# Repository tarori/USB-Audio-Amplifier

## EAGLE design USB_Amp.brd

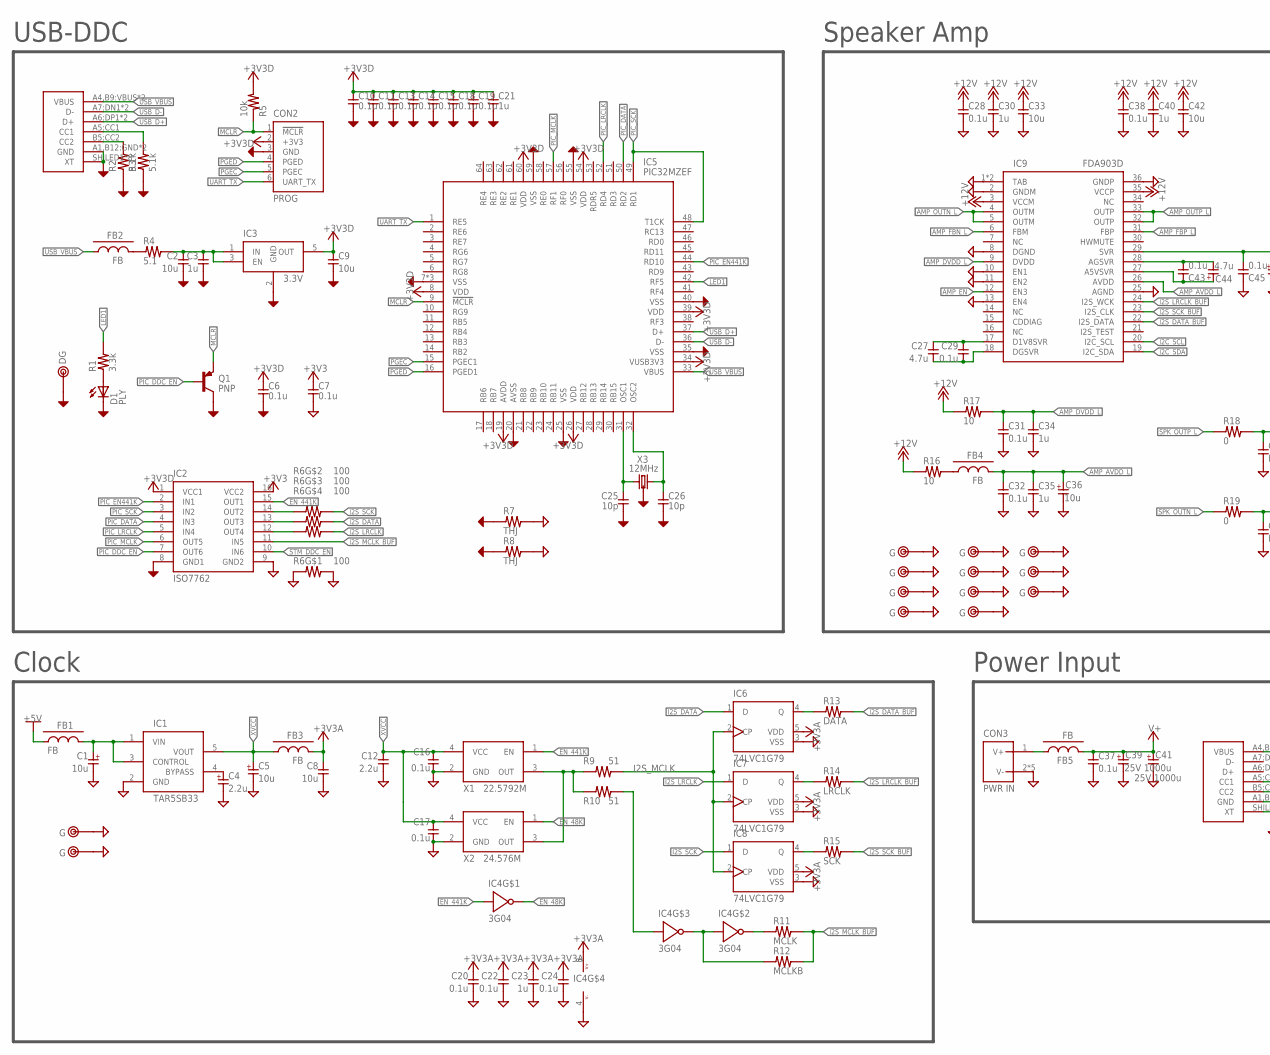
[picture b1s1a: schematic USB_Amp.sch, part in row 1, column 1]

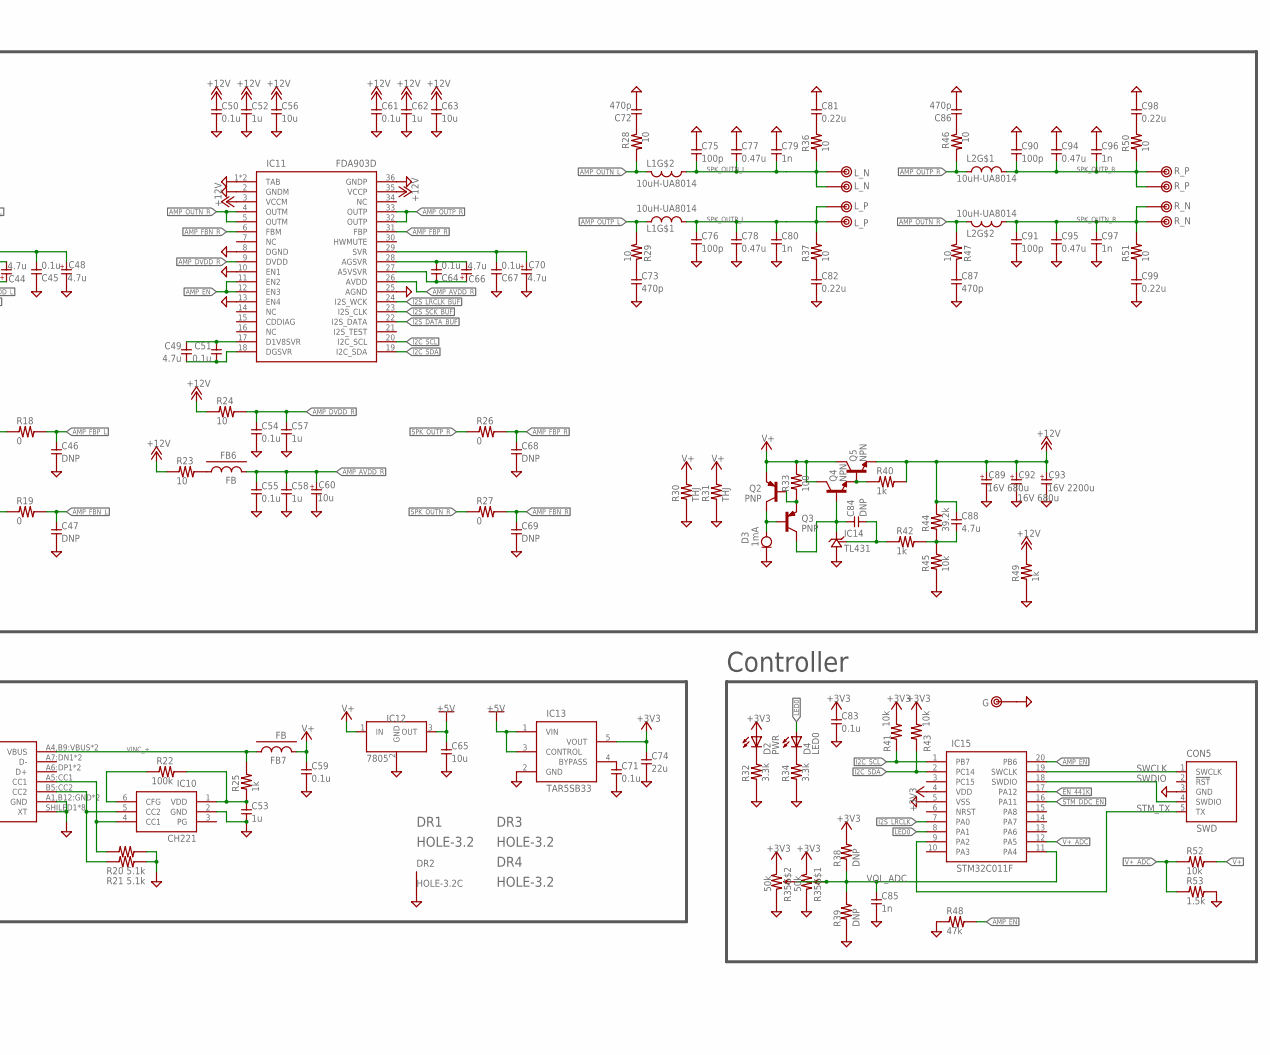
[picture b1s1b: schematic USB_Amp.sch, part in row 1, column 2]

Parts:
C1, C5: 10u; 2012-POL
C2, C8, C9: 10u; 2012
C3, C21, C53: 1u; 1608C
C4: 2.2u; 2012-POL
C6, C10, C11, C13, C14, C15, C16, C17, C18, C19, C37, C59, C71, C83: 0.1u; 1608C
C7, C20, C22, C24, C28, C29, C31, C32, C38, C43, C45, C50, C51, C54, C55, C61, C64, C67: 0.1u; 1005
C12: 2.2u; 2012
C23: 1u; 1005
C25, C26: 10p; 1005
C27, C49: 4.7u; 1608C
C30, C34, C35, C40, C52, C57, C58, C62: 1u; 2012
C33, C42, C56, C63: 10u; 3225
C36, C60: 10u; 3225-POL
C39, C41: 25V 1000u; E5-10
C44, C48, C66, C70: 4.7u; 2012-POL
C46, C47, C68, C69, C84: DNP; 1608C
C65: 10u; 3216
C72, C73, C86, C87: 470p; 1608C
C74: 22u; 2012
C75, C76, C90, C91: 100p; 1608C
C77, C78, C94, C95: 0.47u; C050W
C79, C80, C96, C97: 1n; 2012
C81, C82, C98, C99: 0.22u; 3225
C85: 1n; 1608C
C88: 4.7u; 3216
C89, C92: 16V 680u; E5-10
C93: 16V 2200u; E5-13
CON1: AUDIO_IN; 5077CR-16-SMC2-BK-TR-2OZ
CON2: PROG; 1X06
CON3: PWR IN; 2.1MM_CON
CON4: USB-C-2OZ; 5077CR-16-SMC2-BK-TR-2OZ
CON5: SWD; SWD_CON
D1: PLY; D1608
D2: PWR; LED2.5
D3: 1mA; SOD123
D4: LED0; LED2.5
DR1, DR3, DR4: HOLE-3.2; HOLE_3.2
DR2: HOLE-3.2C; HOLE_3.2_CON2
FB1, FB2, FB3, FB4, FB6: FB; 1608-FB
FB5, FB7: FB; 3216-FB
IC1, IC13: TAR5SB33; SOT23-5
IC2: ISO7762; TSSOP16
IC3: 3.3V; SOT23-5
IC4: 3G04; SSOP8-P-0.65
IC5: PIC32MZEF; QFN64HT
IC6, IC7, IC8: 74LVC1G79; TSSOP5
IC9, IC11: FDA903D; POWER-SSO36
IC10: CH221; SOT23-6
IC12: 7805; DPAK
IC14: TL431; SC59
IC15: STM32C011F; TSSOP20
L1, L2: 10uH-UA8014; UA8014
Q1, Q2, Q3: PNP; SC59
Q4: NPN; SC59
Q5: NPN; SOT223
R1, R32, R34: 3.3k; 1608
R2, R3, R20, R21: 5.1k; 1608
R4: 5.1; 1608
R5, R41, R43, R45, R52: 10k; 1608
R6: 100; EXB28V
R7, R8: THJ; 3216-2
R9, R10: 51; 1005
R11: MCLK; 1005
R12: MCLKB; 1005
R13: DATA; 1005
R14: LRCLK; 1005
R15: SCK; 1005
R16, R17, R23, R24, R28, R29, R46, R47: 10; 1608
R18, R19, R26, R27: 0; 1608
R22: 100k; 1608
R25: 1k; 2012
R30, R31: THJ; 1608-W
R33: 100; 1608
R35: 50k; RK0972
R36, R37, R50, R51: 10; 3216
R38, R39: DNP; 1608
R40, R42: 1k; 1608
R44: 39.2k; 1608
R48: 47k; 1608
R49: 1k; 3216
R53: 1.5k; 1608
TP1: L_N; TESTPIN-BIG
TP2: L_P; TESTPIN-BIG
TP3: R_P; TESTPIN-BIG
TP4: R_N; TESTPIN-BIG
TP5: DG; TESTPIN
TP6, TP7, TP8, TP9, TP10, TP11, TP12, TP13, TP14, TP15, TP16, TP17, TP18, TP24: G; TESTPIN
TP19: L_P; TESTPIN-MID
TP20: L_N; TESTPIN-MID
TP21: R_P; TESTPIN-MID
TP22: R_N; TESTPIN-MID
X1: 22.5792M; KC3225
X2: 24.576M; KC3225
X3: 12MHz; KC3225-CRYSTAL

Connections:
+3V3: C7.1, C74.1, C83.1, D2.A, IC2.16 (VCC2), IC13.5 (VOUT), IC15.4 (VDD), R35.3, R35.6 (3), R38.2, R41.2, R43.2
+3V3A: C8.1, C20.1, C22.1, C23.1, C24.1, FB3.2, IC4.8 (V+), IC6.5 (VDD), IC7.5 (VDD), IC8.5 (VDD)
+3V3D: C6.1, C9.1, C10.1, C11.1, C13.1, C14.1, C15.1, C18.1, C19.1, C21.1, CON2.2 (+3V3), IC2.1 (VCC1), IC3.5 (OUT), IC5.8 (VDD), IC5.19 (AVDD), IC5.26 (VDD), IC5.34 (VUSB3V3), IC5.39 (VDD), IC5.54 (VDD), IC5.60 (VDD), R5.2
+5V: C65.1, FB1.1, IC12.3 (OUT), IC13.1 (VIN), IC13.3 (CONTROL)
+12V: C28.1, C30.1, C33.1, C38.1, C40.1, C42.1, C50.1, C52.1, C56.1, C61.1, C62.1, C63.1, C88.1, C89.+ (1), C92.+ (1), C93.+ (1), IC9.3 (VCCM), IC9.35 (VCCP), IC11.3 (VCCM), IC11.35 (VCCP), Q5.3 (E), R16.1, R17.1, R23.1, R24.1, R40.2, R44.2, R49.2
AMP_1V8_L: C27.1, C29.1, IC9.17 (D1V8SVR)
AMP_1V8_R: C49.1, C51.1, IC11.17 (D1V8SVR)
AMP_5V_L: C43.1, C44.1, IC9.27 (A5VSVR)
AMP_5V_R: C64.1, C66.1, IC11.27 (A5VSVR)
AMP_AVDD_L: C32.1, C35.1, C36.1, FB4.2, IC9.26 (AVDD)
AMP_AVDD_R: C55.1, C58.1, C60.1, FB6.2, IC11.26 (AVDD)
AMP_AVSS_L: C43.2, C44.2, IC9.28 (AGSVR)
AMP_AVSS_R: C64.2, C66.2, IC11.28 (AGSVR)
AMP_DVDD_L: C31.1, C34.1, IC9.9 (DVDD), R17.2
AMP_DVDD_R: C54.1, C57.1, IC11.9 (DVDD), R24.2
AMP_DVSS_L: C27.2, C29.2, IC9.18 (DGSVR)
AMP_DVSS_R: C49.2, C51.2, IC11.18 (DGSVR)
AMP_EN: IC9.12 (EN3), IC11.11 (EN2), IC11.12 (EN3), IC15.20 (PB6), R48.2
AMP_FBN_L: C47.1, IC9.6 (FBM), R19.2
AMP_FBN_R: C69.1, IC11.6 (FBM), R27.2
AMP_FBP_L: C46.1, IC9.31 (FBP), R18.2
AMP_FBP_R: C68.1, IC11.31 (FBP), R26.2
AMP_OUTN_L: IC9.4 (OUTM), IC9.5 (OUTM), L1.4 (2), R28.2
AMP_OUTN_R: IC11.4 (OUTM), IC11.5 (OUTM), L2.4 (2), R47.2
AMP_OUTP_L: IC9.32 (OUTP), IC9.33 (OUTP), L1.1, R29.2
AMP_OUTP_R: IC11.32 (OUTP), IC11.33 (OUTP), L2.1, R46.2
AMP_SVR_L: C45.2, C48.1, IC9.29 (SVR)
AMP_SVR_R: C67.2, C70.1, IC11.29 (SVR)
DGND: C2.2, C3.2, C6.2, C9.2, C10.2, C11.2, C13.2, C14.2, C15.2, C18.2, C19.2, C21.2, C25.2, C26.2, CON1.A1,B12:GND (GND), CON1.B1,A12:GND (GND), CON1.SHILED1 (XT), CON1.SHILED2 (XT), CON1.SHILED3 (XT), CON1.SHILED4 (XT), CON1.SHILED5 (XT), CON1.SHILED6 (XT), CON1.SHILED7 (XT), CON1.SHILED8 (XT), CON2.3 (GND), D1.K, IC2.8 (GND1), IC3.2 (GND), IC5.7 (VSS), IC5.20 (AVSS), IC5.25 (VSS), IC5.35 (VSS), IC5.40 (VSS), IC5.55 (VSS), IC5.59 (VSS), IC5.HT (VSS), IC5.HT2 (VSS), Q1.3 (C), R2.1, R3.1, R7.1, R8.1, TP5.1, X3.2 (GND), X3.4 (GND)
EN_48K: IC4.7 (OUT), X2.1 (EN)
EN_441K: IC2.15 (OUT1), IC4.1 (IN), IC15.17 (PA12), X1.1 (EN)
GND: C1.2, C4.2, C5.2, C7.2, C8.2, C12.2, C16.2, C17.2, C20.2, C22.2, C23.2, C24.2, C28.2, C30.2, C31.2, C32.2, C33.2, C34.2, C35.2, C36.2, C37.2, C38.2, C39.- (2), C40.2, C41.- (2), C42.2, C45.1, C46.2, C47.2, C48.2, C50.2, C52.2, C53.2, C54.2, C55.2, C56.2, C57.2, C58.2, C59.2, C60.2, C61.2, C62.2, C63.2, C65.2, C67.1, C68.2, C69.2, C70.2, C71.2, C72.2, C73.2, C74.2, C75.1, C76.2, C77.1, C77.3 (1), C78.2, C78.4 (2), C79.1, C80.2, C81.1, C82.2, C83.2, C85.2, C86.2, C87.2, C89.- (2), C90.1, C91.2, C92.- (2), C93.- (2), C94.1, C94.3 (1), C95.2, C95.4 (2), C96.1, C97.2, C98.1, C99.2, CON3.2 (V-), CON3.3 (V-), CON3.4 (V-), CON3.5 (V-), CON3.6 (V-), CON4.A1,B12:GND (GND), CON4.B1,A12:GND (GND), CON4.SHILED1 (XT), CON4.SHILED2 (XT), CON4.SHILED3 (XT), CON4.SHILED4 (XT), CON4.SHILED5 (XT), CON4.SHILED6 (XT), CON4.SHILED7 (XT), CON4.SHILED8 (XT), CON5.3 (GND), D3.2 (K), DR2.T, IC1.2 (GND), IC2.9 (GND2), IC4.4 (V-), IC6.3 (VSS), IC7.3 (VSS), IC8.3 (VSS), IC9.1 (TAB), IC9.2 (GNDM), IC9.8 (DGND), IC9.10 (EN1), IC9.11 (EN2), IC9.13 (EN4), IC9.25 (AGND), IC9.36 (GNDP), IC9.HT (TAB), IC10.2 (GND), IC11.1 (TAB), IC11.2 (GNDM), IC11.8 (DGND), IC11.10 (EN1), IC11.13 (EN4), IC11.25 (AGND), IC11.36 (GNDP), IC11.HT (TAB), IC12.2 (GND), IC13.2 (GND), IC14.3 (GND), IC15.5 (VSS), R6.1, R6.8 (2), R7.2, R8.2, R20.2, R21.2, R30.1, R31.1, R32.1, R34.1, R35.1, R35.4 (1), R39.1, R45.1, R48.1, R49.1, R53.2, TP6.1, TP7.1, TP8.1, TP9.1, TP10.1, TP11.1, TP12.1, TP13.1, TP14.1, TP15.1, TP16.1, TP17.1, TP18.1, TP24.1, X1.2 (GND), X2.2 (GND)
I2C_SCL: IC9.20 (I2C_SCL), IC11.20 (I2C_SCL), IC15.1 (PB7), R41.1
I2C_SDA: IC9.19 (I2C_SDA), IC11.19 (I2C_SDA), IC15.2 (PC14), R43.1
I2S_DATA: IC6.1 (D), R6.6 (2)
I2S_DATA_BUF: IC9.22 (I2S_DATA), IC11.22 (I2S_DATA), R13.2
I2S_LRCLK: IC7.1 (D), IC15.7 (PA0), R6.5 (2)
I2S_LRCLK_BUF: IC9.24 (I2S_WCK), IC11.24 (I2S_WCK), R14.2
I2S_MCLK: IC6.2 (CP), IC7.2 (CP), IC8.2 (CP), R9.2
I2S_MCLK2: IC4.3 (IN), R10.2
I2S_MCLK_BUF: IC2.11 (IN5), R11.2, R12.2
I2S_SCK: IC8.1 (D), R6.7 (2)
I2S_SCK_BUF: IC9.23 (I2S_CLK), IC11.23 (I2S_CLK), R15.2
LED0: D4.A, IC15.8 (PA1)
LED1: IC5.42 (RF5), R1.2
MCLK_OSC: R9.1, R10.1, X1.3 (OUT), X2.3 (OUT)
MCLR: CON2.1 (!MCLR), IC5.9 (!MCLR), Q1.2 (E), R5.1
unnamed: CON1.B5:CC2 (CC2), R2.2
unnamed: CON1.A5:CC1 (CC1), R3.2
unnamed: FB2.2, R4.1
unnamed: C2.1, C3.1, IC3.1 (IN), IC3.3 (EN), R4.2
unnamed: C25.1, IC5.31 (OSC1), X3.3 (2)
unnamed: C81.2, R36.2
unnamed: C26.1, IC5.32 (OSC2), X3.1
unnamed: IC2.14 (OUT2), R6.2 (1)
unnamed: D1.A, R1.1
unnamed: IC6.4 (Q), R13.1
unnamed: IC7.4 (Q), R14.1
unnamed: IC8.4 (Q), R15.1
unnamed: C82.1, R37.1
unnamed: Q4.2 (E), Q5.1 (B), R40.1
unnamed: C99.1, R51.1
unnamed: C84.2, IC14.1 (REF), R42.1
unnamed: C98.2, R50.2
unnamed: IC2.13 (OUT3), R6.3 (1)
unnamed: C4.1, IC1.4 (BYPASS)
unnamed: IC2.12 (OUT4), R6.4 (1)
unnamed: C84.1, IC14.2 (OUT), Q3.3 (C), Q4.1 (B)
unnamed: FB6.1, R23.2
unnamed: Q2.1 (B), Q3.2 (E), R33.1
unnamed: C88.2, R42.2, R44.1, R45.2
unnamed: CON4.A5:CC1 (CC1), IC10.4 (CC1), R20.1
unnamed: CON4.B5:CC2 (CC2), IC10.5 (CC2), R21.1
unnamed: C53.1, IC10.1 (VDD), R22.2, R25.1
unnamed: IC10.6 (CFG), R22.1
unnamed: C71.1, IC13.4 (BYPASS)
unnamed: D2.K, R32.2
unnamed: IC4.5 (OUT), IC4.6 (IN), R12.1
unnamed: D3.1 (A), Q2.3 (C), Q3.1 (B)
unnamed: IC4.2 (OUT), R11.1
unnamed: C72.1, R28.1
unnamed: D4.K, R34.2
unnamed: C1.1, FB1.2, IC1.1 (VIN), IC1.3 (CONTROL)
unnamed: C87.1, R47.1
unnamed: C73.1, R29.1
unnamed: C86.1, R46.1
unnamed: FB4.1, R16.2
PGEC: CON2.5 (PGEC), IC5.15 (PGEC1)
PGED: CON2.4 (PGED), IC5.16 (PGED1)
PIC_DATA: IC2.4 (IN3), IC5.50 (RD2)
PIC_DDC_EN: IC2.7 (OUT6), Q1.1 (B)
PIC_EN441K: IC2.2 (IN1), IC5.44 (RD10)
PIC_LRCLK: IC2.5 (IN4), IC5.52 (RD4)
PIC_MCLK: IC2.6 (OUT5), IC5.57 (RF1)
PIC_SCK: IC2.3 (IN2), IC5.48 (T1CK), IC5.49 (RD1)
SPK_OUTN_L: C75.2, C77.2, C77.4 (2), C79.2, L1.3 (1), R19.1, R36.1, TP1.1, TP20.1
SPK_OUTN_R: C91.1, C95.1, C95.3 (1), C97.1, L2.3 (1), R27.1, R51.2, TP4.1, TP22.1
SPK_OUTP_L: C76.1, C78.1, C78.3 (1), C80.1, L1.2, R18.1, R37.2, TP2.1, TP19.1
SPK_OUTP_R: C90.2, C94.2, C94.4 (2), C96.2, L2.2, R26.1, R50.1, TP3.1, TP21.1
STM_DDC_EN: IC2.10 (IN6), IC15.16 (PA11)
STM_TX: CON5.5 (TX), IC15.9 (PA2)
SWCLK: CON5.1 (SWCLK), IC15.19 (SWCLK)
SWDIO: CON5.4 (SWDIO), IC15.18 (SWDIO)
UART_TX: CON2.6 (UART_TX), IC5.1 (RE5)
USB_D+: CON1.A6:DP1 (D+), CON1.B6:DP2 (D+), IC5.37 (D+)
USB_D-: CON1.A7:DN1 (D-), CON1.B7:DN2 (D-), IC5.36 (D-)
USB_VBUS: CON1.A4,B9:VBUS (VBUS), CON1.B4,A9:VBUS (VBUS), FB2.1, IC5.33 (VBUS)
V+: C37.1, C39.+ (1), C41.+ (1), C59.1, FB5.2, FB7.2, IC12.1 (IN), Q2.2 (E), Q4.3 (C), Q5.2 (C), Q5.4 (C), R30.2, R31.2, R33.2, R52.2
V+_ADC: IC15.12 (PA5), R52.1, R53.1
VIN+: CON3.1 (V+), FB5.1
VINC_+: CON4.A4,B9:VBUS (VBUS), CON4.B4,A9:VBUS (VBUS), FB7.1, R25.2
VOL_ADC: C85.1, IC15.11 (PA4), R35.2, R35.5 (2), R38.1, R39.2
XVCC: C5.1, C12.1, C16.1, C17.1, FB3.1, IC1.5 (VOUT), X1.4 (VCC), X2.4 (VCC)

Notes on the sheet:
USB-DDC
Speaker Amp
Power Input
Controller
Clock

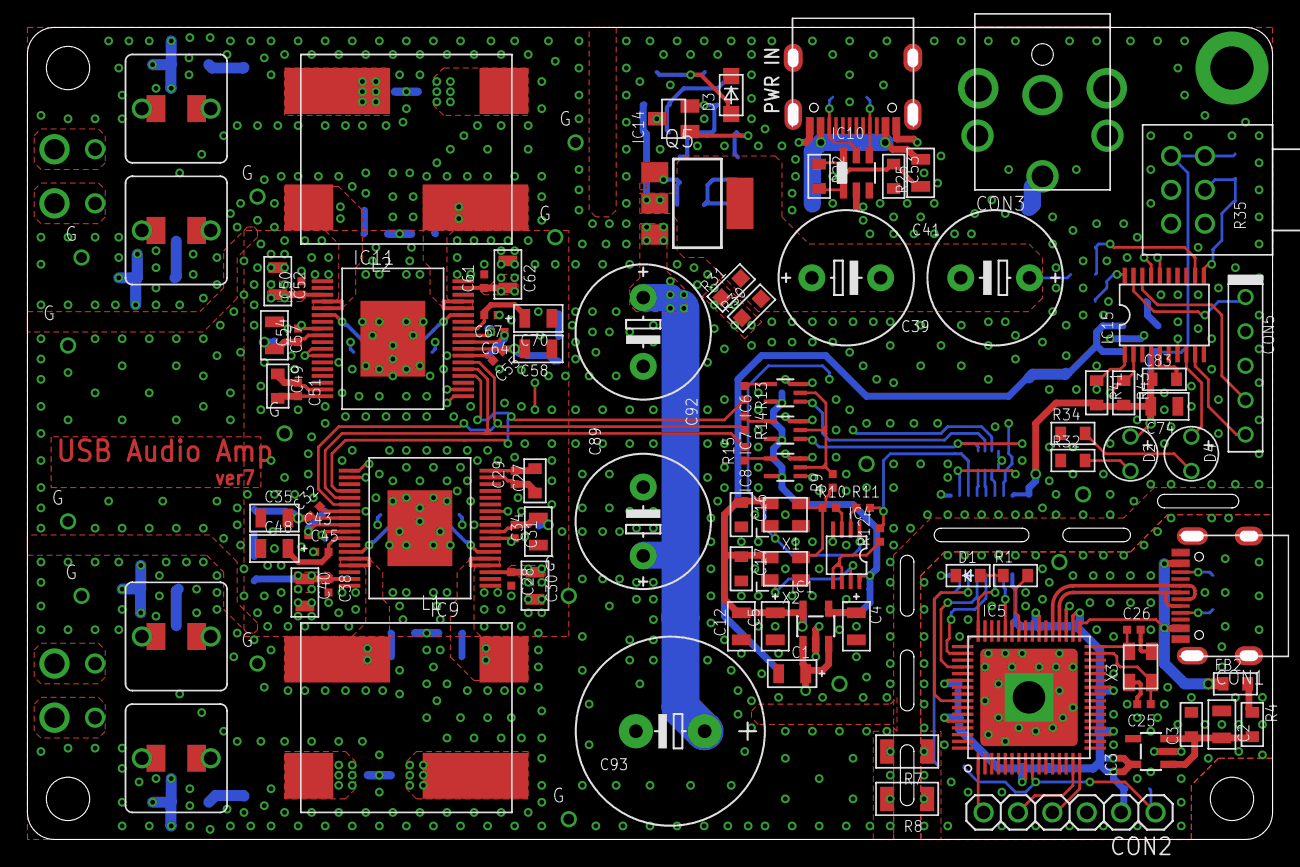
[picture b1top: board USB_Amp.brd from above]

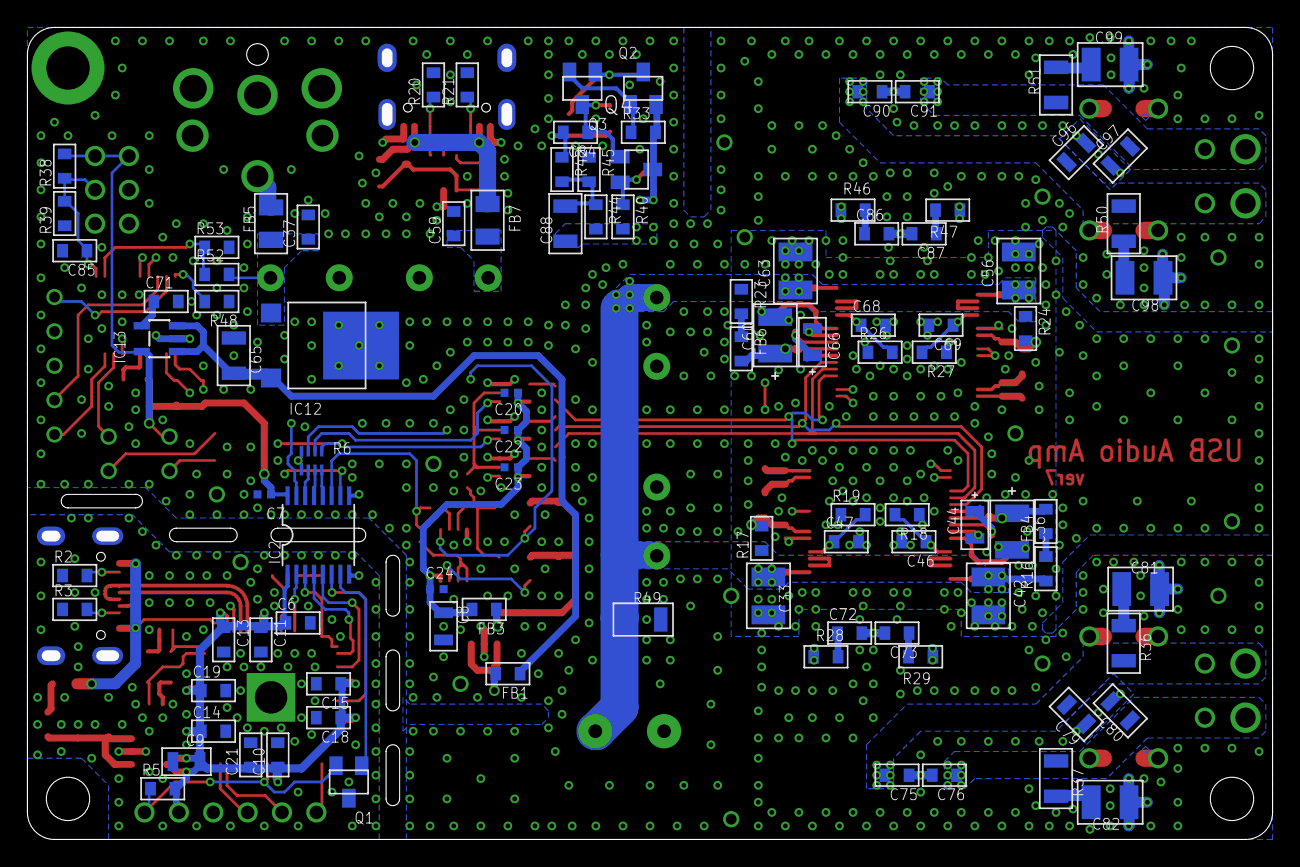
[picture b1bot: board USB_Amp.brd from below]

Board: 4 copper layers, 92.0 x 60.0 mm, 220 parts (97 on the bottom side), 113 nets.

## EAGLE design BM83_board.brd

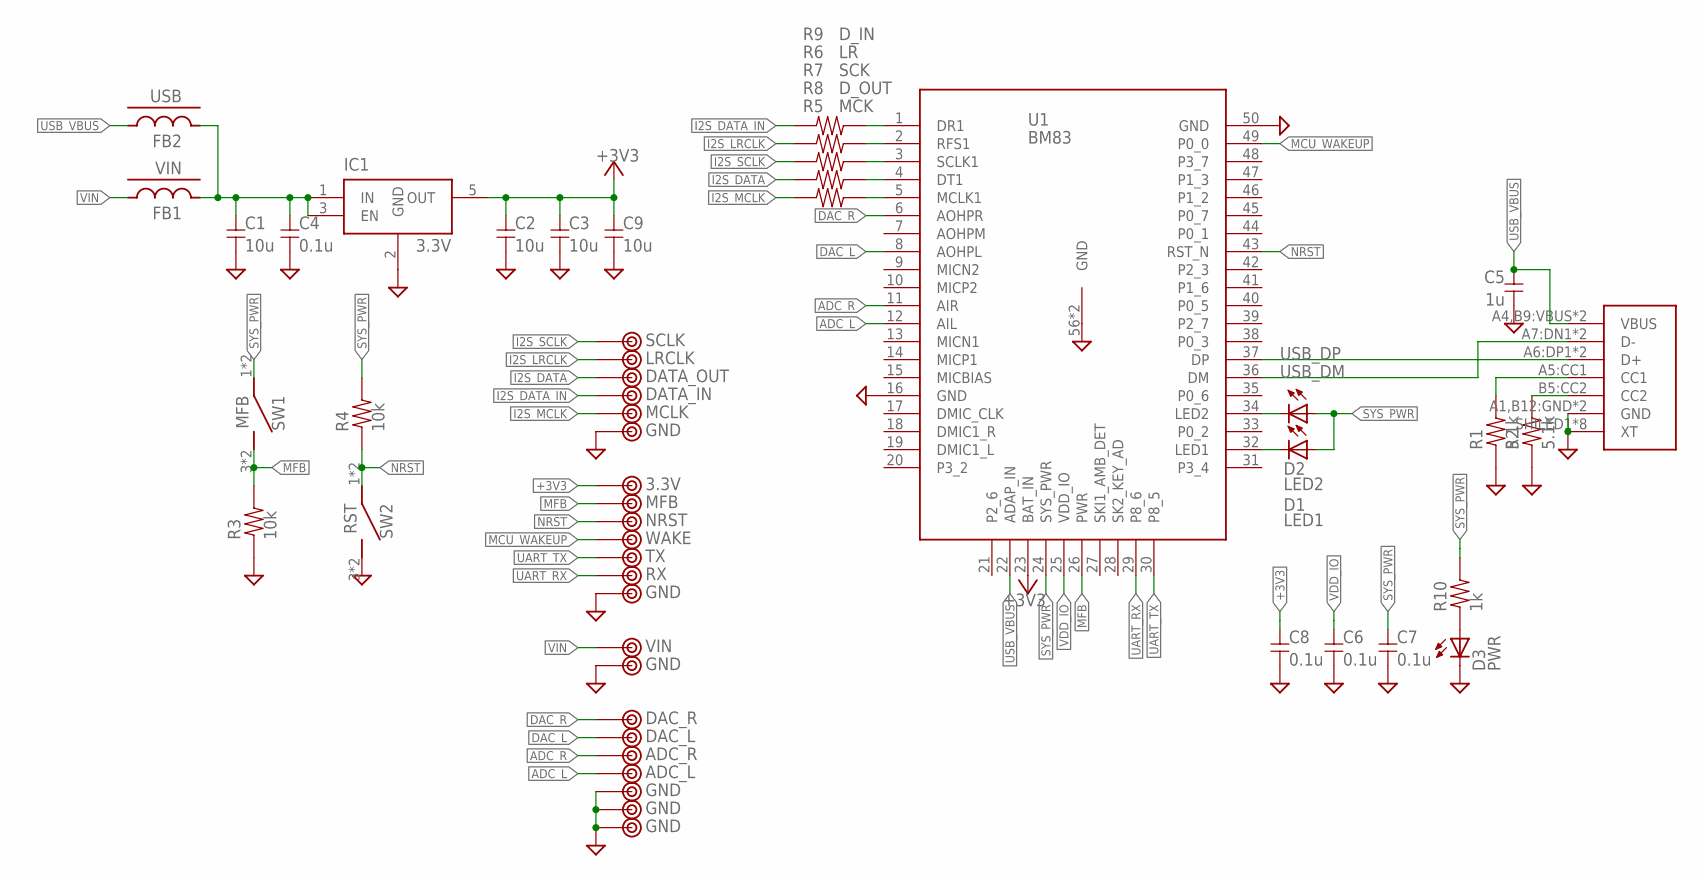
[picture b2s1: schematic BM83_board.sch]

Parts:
C1, C2, C3, C9: 10u; 2012
C4, C6, C7, C8: 0.1u; 1608C
C5: 1u; 1608C
CON1: USB-C; 5077CR-16-SMC2-BK-TR
D1: LED1; D1608
D2: LED2; D1608
D3: PWR; D1608
FB1: VIN; 1608-FB
FB2: USB; 1608-FB
IC1: 3.3V; SOT23-5
R1, R2: 5.1k; 1608
R3, R4: 10k; 1608
R5: MCK; 1608-2
R6: LR; 1608-2
R7: SCK; 1608-2
R8: D_OUT; 1608-2
R9: D_IN; 1608-2
R10: 1k; 1608
SW1: MFB; SKRPACE010
SW2: RST; SKRPACE010
TP1: DAC_R; TESTPIN
TP2: DAC_L; TESTPIN
TP3, TP9, TP16, TP18, TP21, TP22: GND; TESTPIN
TP4: SCLK; TESTPIN
TP5: LRCLK; TESTPIN
TP6: DATA_OUT; TESTPIN
TP7: DATA_IN; TESTPIN
TP8: MCLK; TESTPIN
TP10: 3.3V; TESTPIN
TP11: MFB; TESTPIN
TP12: NRST; TESTPIN
TP13: WAKE; TESTPIN
TP14: TX; TESTPIN
TP15: RX; TESTPIN
TP17: VIN; TESTPIN
TP19: ADC_R; TESTPIN
TP20: ADC_L; TESTPIN
U1: BM83

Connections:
+3V3: C2.1, C3.1, C8.1, C9.1, IC1.5 (OUT), TP10.1, U1.23 (BAT_IN)
ADC_L: TP20.1, U1.12 (AIL)
ADC_R: TP19.1, U1.11 (AIR)
DAC_L: TP2.1, U1.8 (AOHPL)
DAC_R: TP1.1, U1.6 (AOHPR)
GND: C1.2, C2.2, C3.2, C4.2, C5.2, C6.2, C7.2, C8.2, C9.2, CON1.A1,B12:GND (GND), CON1.B1,A12:GND (GND), CON1.SHILED1 (XT), CON1.SHILED2 (XT), CON1.SHILED3 (XT), CON1.SHILED4 (XT), CON1.SHILED5 (XT), CON1.SHILED6 (XT), CON1.SHILED7 (XT), CON1.SHILED8 (XT), D3.K, IC1.2 (GND), R1.1, R2.1, R3.1, SW2.3 (2), SW2.4 (2), TP3.1, TP9.1, TP16.1, TP18.1, TP21.1, TP22.1, U1.16 (GND), U1.50 (GND), U1.56 (GND), U1.57 (GND)
I2S_DATA: R8.1, TP6.1
I2S_DATA_IN: R9.1, TP7.1
I2S_LRCLK: R6.1, TP5.1
I2S_MCLK: R5.1, TP8.1
I2S_SCLK: R7.1, TP4.1
MCU_WAKEUP: TP13.1, U1.49 (P0_0)
MFB: R3.2, SW1.3 (2), SW1.4 (2), TP11.1, U1.26 (PWR)
unnamed: CON1.B5:CC2 (CC2), R2.2
unnamed: CON1.A5:CC1 (CC1), R1.2
unnamed: R5.2, U1.5 (MCLK1)
unnamed: D2.K, U1.34 (LED2)
unnamed: D1.K, U1.32 (LED1)
unnamed: C1.1, C4.1, FB1.2, FB2.2, IC1.1 (IN), IC1.3 (EN)
unnamed: D3.A, R10.1
unnamed: R8.2, U1.4 (DT1)
unnamed: R7.2, U1.3 (SCLK1)
unnamed: R6.2, U1.2 (RFS1)
unnamed: R9.2, U1.1 (DR1)
NRST: R4.1, SW2.1, SW2.2 (1), TP12.1, U1.43 (RST_N)
SYS_PWR: C7.1, D1.A, D2.A, R4.2, R10.2, SW1.1, SW1.2 (1), U1.24 (SYS_PWR)
UART_RX: TP15.1, U1.29 (P8_6)
UART_TX: TP14.1, U1.30 (P8_5)
USB_DM: CON1.A7:DN1 (D-), CON1.B7:DN2 (D-), U1.36 (DM)
USB_DP: CON1.A6:DP1 (D+), CON1.B6:DP2 (D+), U1.37 (DP)
USB_VBUS: C5.1, CON1.A4,B9:VBUS (VBUS), CON1.B4,A9:VBUS (VBUS), FB2.1, U1.22 (ADAP_IN)
VDD_IO: C6.1, U1.25 (VDD_IO)
VIN: FB1.1, TP17.1

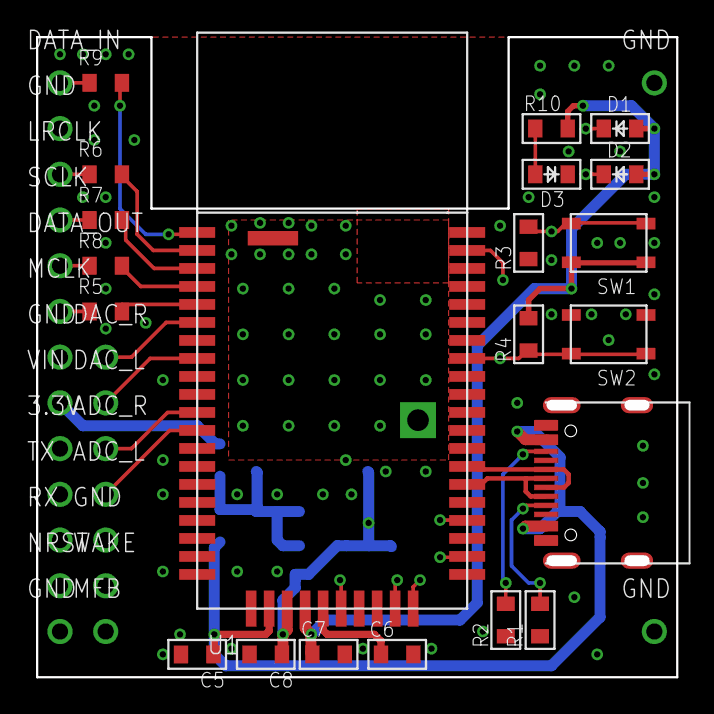
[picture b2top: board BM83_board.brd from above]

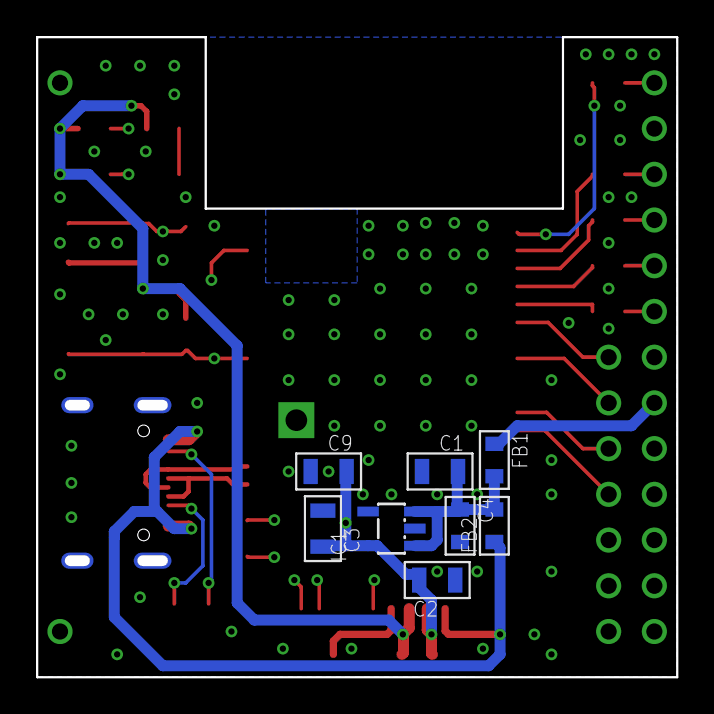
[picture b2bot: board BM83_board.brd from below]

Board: 4 copper layers, 35.6 x 35.6 mm, 51 parts (8 on the bottom side), 33 nets.

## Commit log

2024-08-10 TAS2770
2024-08-11 ver2
2024-08-22 インダクタ変更
2025-01-10 BM83 test
2025-07-02 取り合えず
2025-07-03 定電流源強化
2025-07-19 MCLK配線修正
2025-08-04 ver5.1
2026-01-02 TAS6424対応
2026-01-03 CH1/4に変更
2026-03-07 v4 発注
2026-03-07 新レイアウト途中
2026-03-08 こんな感じ
2026-03-10 v4.2 発注
2026-04-05 v4.3
2026-05-18 FDA903D 発注
